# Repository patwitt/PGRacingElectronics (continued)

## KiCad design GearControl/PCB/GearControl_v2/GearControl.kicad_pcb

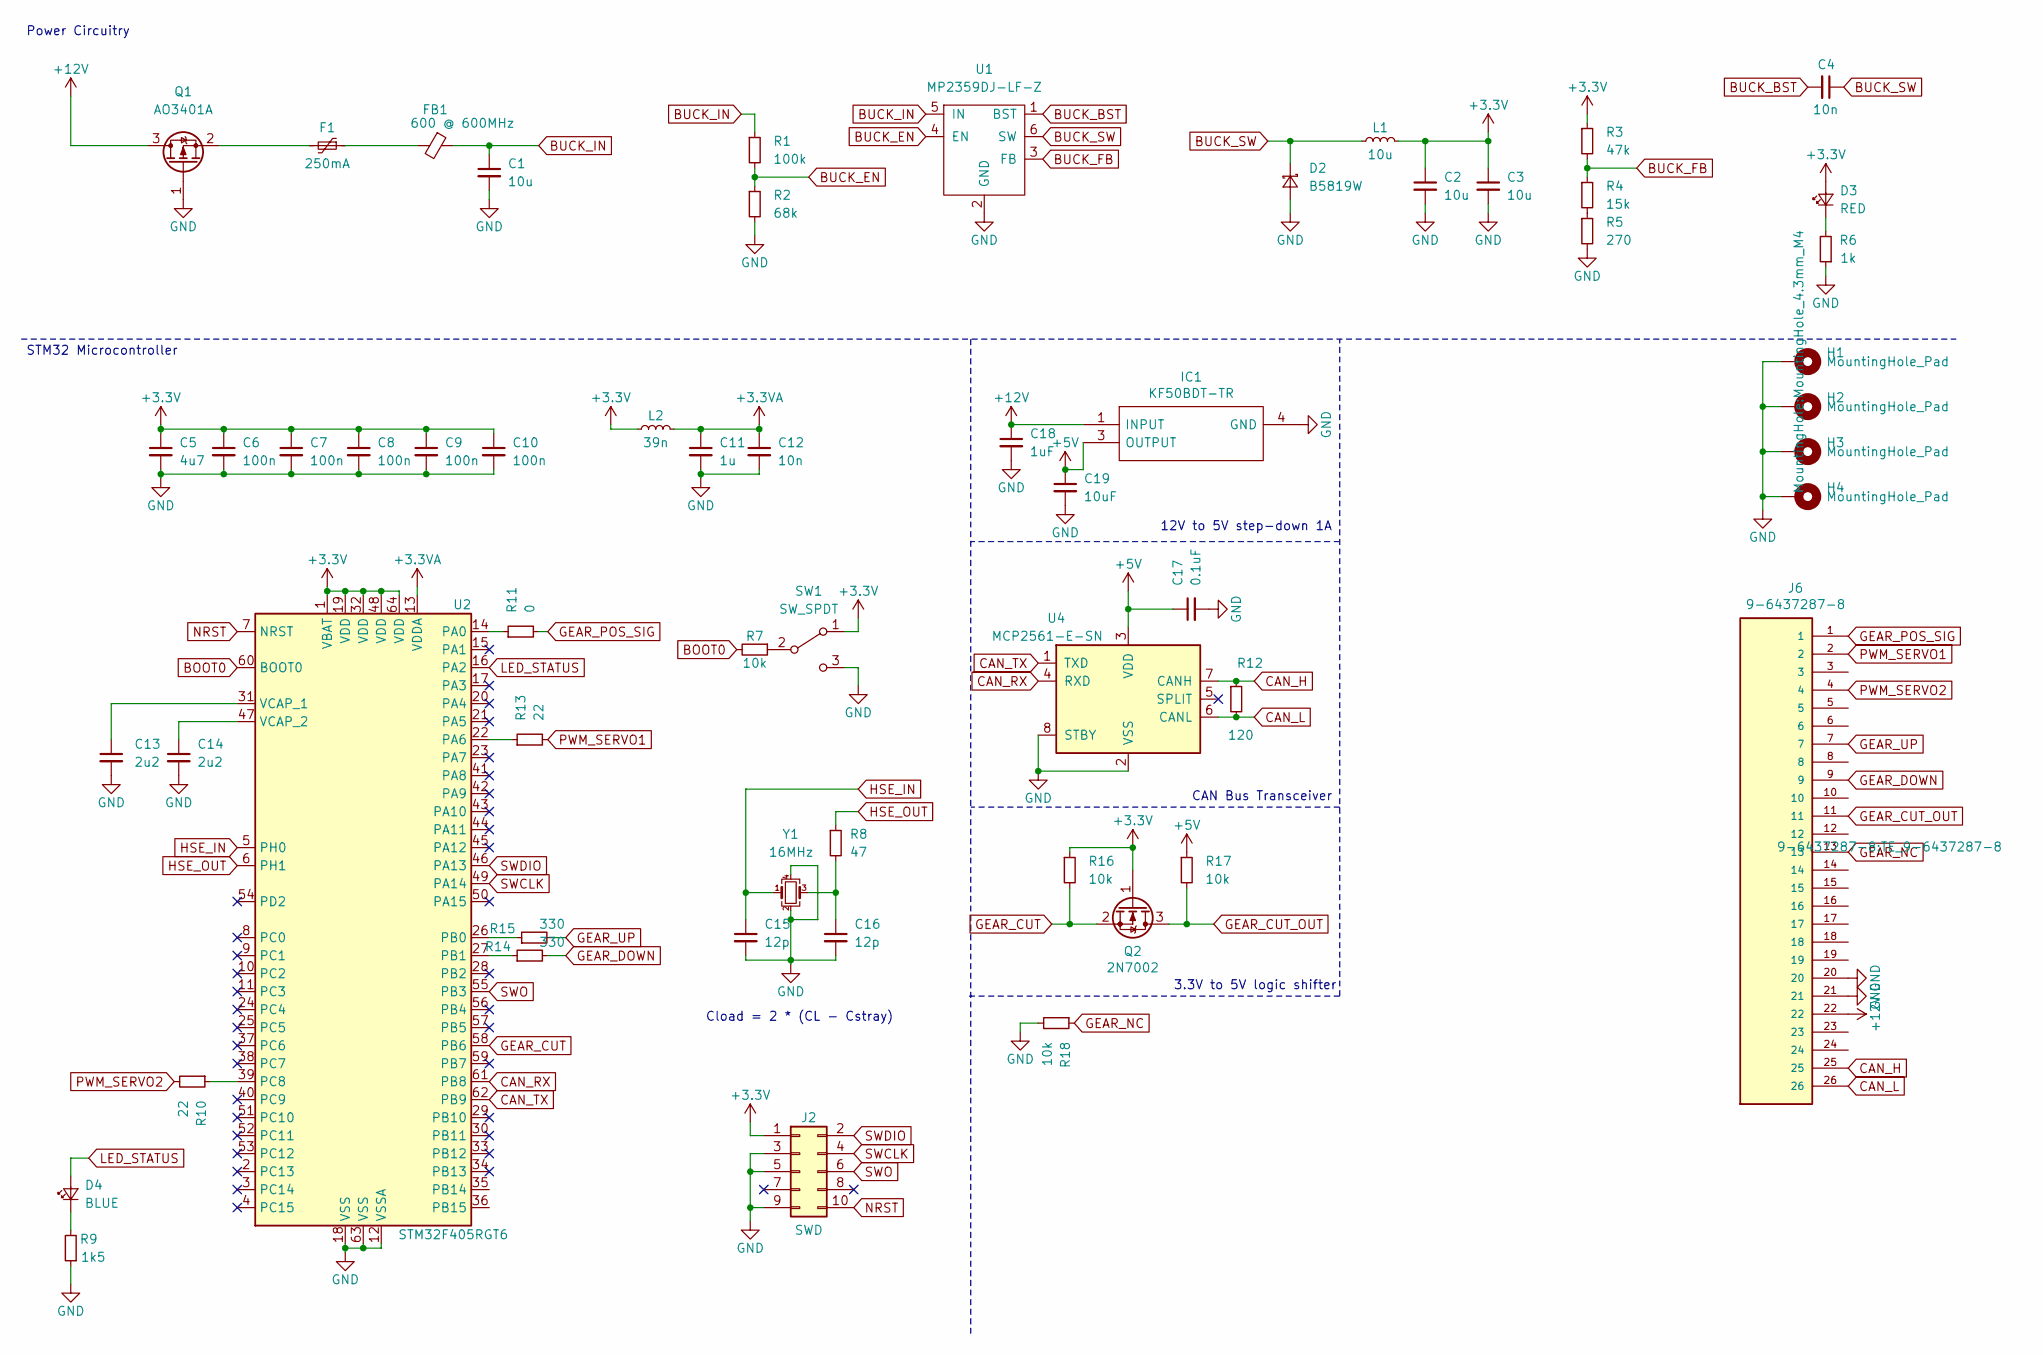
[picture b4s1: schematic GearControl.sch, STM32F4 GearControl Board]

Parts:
C1, C2, C3: 10u; C_1206_3216Metric; LCSC Part # C13585
C4: 10n; C_0603_1608Metric; LCSC Part # C57112
C5: 4u7; C_0603_1608Metric; LCSC Part # C19666
C6, C7, C8, C9, C10: 100n; C_0402_1005Metric; LCSC Part # C1525
C11: 1u; C_0402_1005Metric; LCSC Part # C52923
C12: 10n; C_0402_1005Metric; LCSC Part # C15195
C13, C14: 2u2; C_0603_1608Metric; LCSC Part # C23630
C15, C16: 12p; C_0402_1005Metric; LCSC Part # C1547
C17: 0.1uF; C_0603_1608Metric; LCSC Part # C23630
C18: 1uF; C_0805_2012Metric; LCSC Part # C1525
C19: 10uF; C_0805_2012Metric; LCSC Part # C1525
D2: B5819W; D_SOD-123; LCSC Part # C8598
D3: RED; LED_0603_1608Metric; LCSC Part # C2286
D4: BLUE; LED_0603_1608Metric; LCSC Part # C72041
F1: 250mA; Fuse_1206_3216Metric; LCSC Part # C369159
FB1: 600 @ 600MHz; L_0805_2012Metric; LCSC Part # C1017
H1, H2, H3, H4: MountingHole_Pad; MountingHole_4.3mm_M4
IC1: KF50BDT-TR; DPAK; Manufacturer_Part_Number KF50BDT-TR; Mouser Part Number 511-KF50BDT-TR
J2: SWD; PinHeader_2x05_P1.27mm_Vertical_SMD
J6: 9-6437287-8; TE_9-6437287-8; PARTREV A1
L1: 10u; L_Sunlord_MWSA0518_5.4x5.2mm; LCSC Part # C139506
L2: 39n; L_0402_1005Metric; LCSC Part # C26443
Q1: AO3401A; SOT-23; LCSC Part # C15127
Q2: 2N7002; SOT-23
R1: 100k; R_0603_1608Metric; LCSC Part # C25803
R2: 68k; R_0603_1608Metric; LCSC Part # C23231
R3: 47k; R_0603_1608Metric; LCSC Part # C25819
R4: 15k; R_0603_1608Metric; LCSC Part # C22809
R5: 270; R_0603_1608Metric; LCSC Part # C22966
R6: 1k; R_0603_1608Metric; LCSC Part # C21190
R7: 10k; R_0402_1005Metric; LCSC Part # C25744
R8: 47; R_0402_1005Metric; LCSC Part # C25118
R9: 1k5; R_0603_1608Metric; LCSC Part # C22843
R10, R13: 22; R_0603_1608Metric; LCSC Part # C25803
R11: 0; R_0603_1608Metric; LCSC Part # C25803
R12: 120; R_0603_1608Metric
R14, R15: 330; R_0603_1608Metric; LCSC Part # C25803
R16, R17, R18: 10k; R_0603_1608Metric; LCSC Part # C23231
SW1: SW_SPDT; SW_SPDT_PCM12
U1: MP2359DJ-LF-Z; SOT-23-6; LCSC Part # C14259
U2: STM32F405RGT6; LQFP-64_10x10mm_P0.5mm; LCSC Part # C15742
U4: MCP2561-E-SN; SOIC-8_3.9x4.9mm_P1.27mm
Y1: 16MHz; Crystal_SMD_3225-4Pin_3.2x2.5mm; LCSC Part # C13738

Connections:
+3.3VA: C11.1, C12.1, L2.2, U2.13 (VDDA)
+3V3: C2.1, C3.1, C5.1, C6.1, C7.1, C8.1, C9.1, C10.1, D3.2 (A), J2.1, L1.2, L2.1, Q2.1 (G), R3.1, R16.1, SW1.1 (A), U2.1 (VBAT), U2.19 (VDD), U2.32 (VDD), U2.48 (VDD), U2.64 (VDD)
+5V: C17.1, C19.1, IC1.3 (OUTPUT), R17.1, U4.3 (VDD)
+12V: C18.1, IC1.1 (INPUT), J6.22, Q1.3 (D)
BOOT0: R7.2, U2.60 (BOOT0)
BUCK_BST: C4.2, U1.1 (BST)
BUCK_EN: R1.2, R2.1, U1.4 (EN)
BUCK_FB: R3.2, R4.1, U1.3 (FB)
BUCK_IN: C1.1, FB1.1, R1.1, U1.5 (IN)
BUCK_SW: C4.1, D2.1 (K), L1.1, U1.6 (SW)
CAN_H: J6.25, R12.1, U4.7 (CANH)
CAN_L: J6.26, R12.2, U4.6 (CANL)
CAN_RX: U2.61 (PB8), U4.4 (RXD)
CAN_TX: U2.62 (PB9), U4.1 (TXD)
GEAR_CUT: Q2.2 (S), R16.2, U2.58 (PB6)
GEAR_CUT_OUT: J6.11, Q2.3 (D), R17.2
GEAR_DOWN: J6.9, R14.2
GEAR_NC: J6.13, R18.1
GEAR_POS_SIG: J6.1, R11.2
GEAR_UP: J6.7, R15.2
GND: C1.2, C2.2, C3.2, C5.2, C6.2, C7.2, C8.2, C9.2, C10.2, C11.2, C12.2, C13.2, C14.2, C15.2, C16.2, C17.2, C18.2, C19.2, D2.2 (A), H1.1, H2.1, H3.1, H4.1, IC1.4 (GND), J2.3, J2.5, J2.9, J6.20, J6.21, Q1.1 (G), R2.2, R5.2, R6.1, R9.1, R18.2, SW1.3 (C), U1.2 (GND), U2.12 (VSSA), U2.18 (VSS), U2.63 (VSS), U4.2 (VSS), U4.8 (STBY), Y1.2, Y1.4
HSE_IN: C15.1, U2.5 (PH0), Y1.1
HSE_OUT: R8.1, U2.6 (PH1)
LED_STATUS: D4.2 (A), U2.16 (PA2)
NRST: J2.10, U2.7 (NRST)
unnamed: C13.1, U2.31 (VCAP_1)
unnamed: C14.1, U2.47 (VCAP_2)
unnamed: C16.1, R8.2, Y1.3
unnamed: D3.1 (K), R6.2
unnamed: D4.1 (K), R9.2
unnamed: F1.1, FB1.2
unnamed: F1.2, Q1.2 (S)
unnamed: R4.2, R5.1
unnamed: R7.1, SW1.2 (B)
unnamed: R10.1, U2.39 (PC8)
unnamed: R11.1, U2.14 (PA0)
unnamed: R13.1, U2.22 (PA6)
unnamed: R14.1, U2.27 (PB1)
unnamed: R15.1, U2.26 (PB0)
PWM_SERVO1: J6.2, R13.2
PWM_SERVO2: J6.4, R10.2
SWCLK: J2.4, U2.49 (PA14)
SWDIO: J2.2, U2.46 (PA13)
SWO: J2.6, U2.55 (PB3)

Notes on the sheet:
Cload = 2 * (CL - Cstray)
STM32 Microcontroller
Power Circuitry
CAN Bus Transceiver
12V to 5V step-down 1A
3.3V to 5V logic shifter

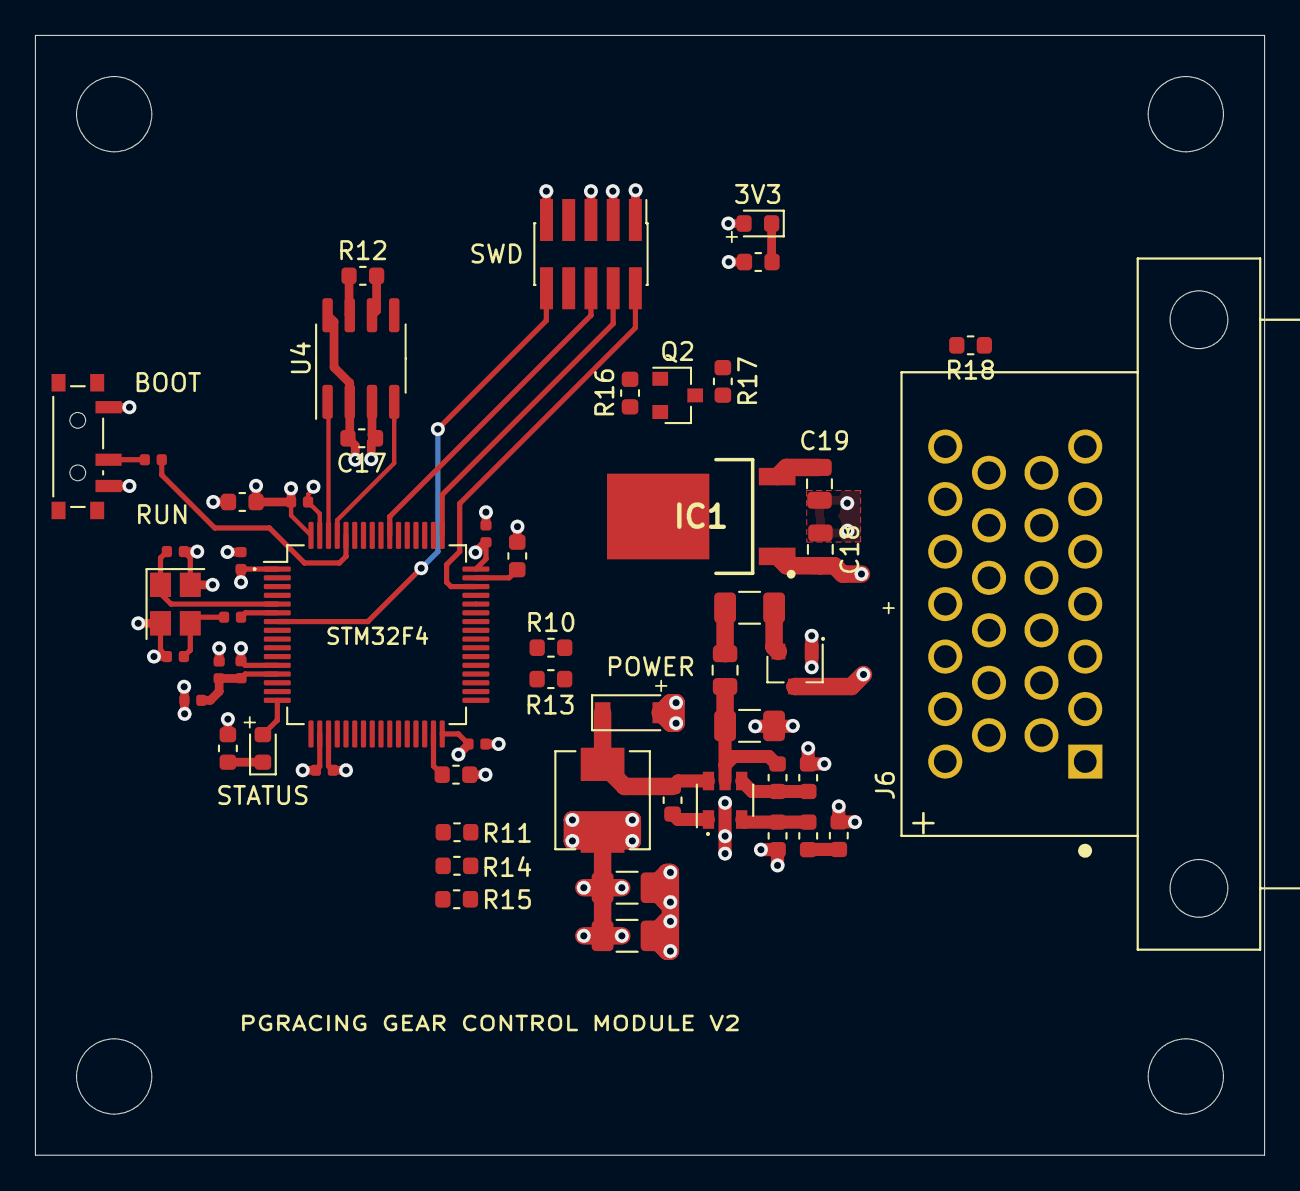
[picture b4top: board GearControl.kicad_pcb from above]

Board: 4 copper layers, 70.2 x 64.0 mm, 58 parts (0 on the bottom side), 44 nets.

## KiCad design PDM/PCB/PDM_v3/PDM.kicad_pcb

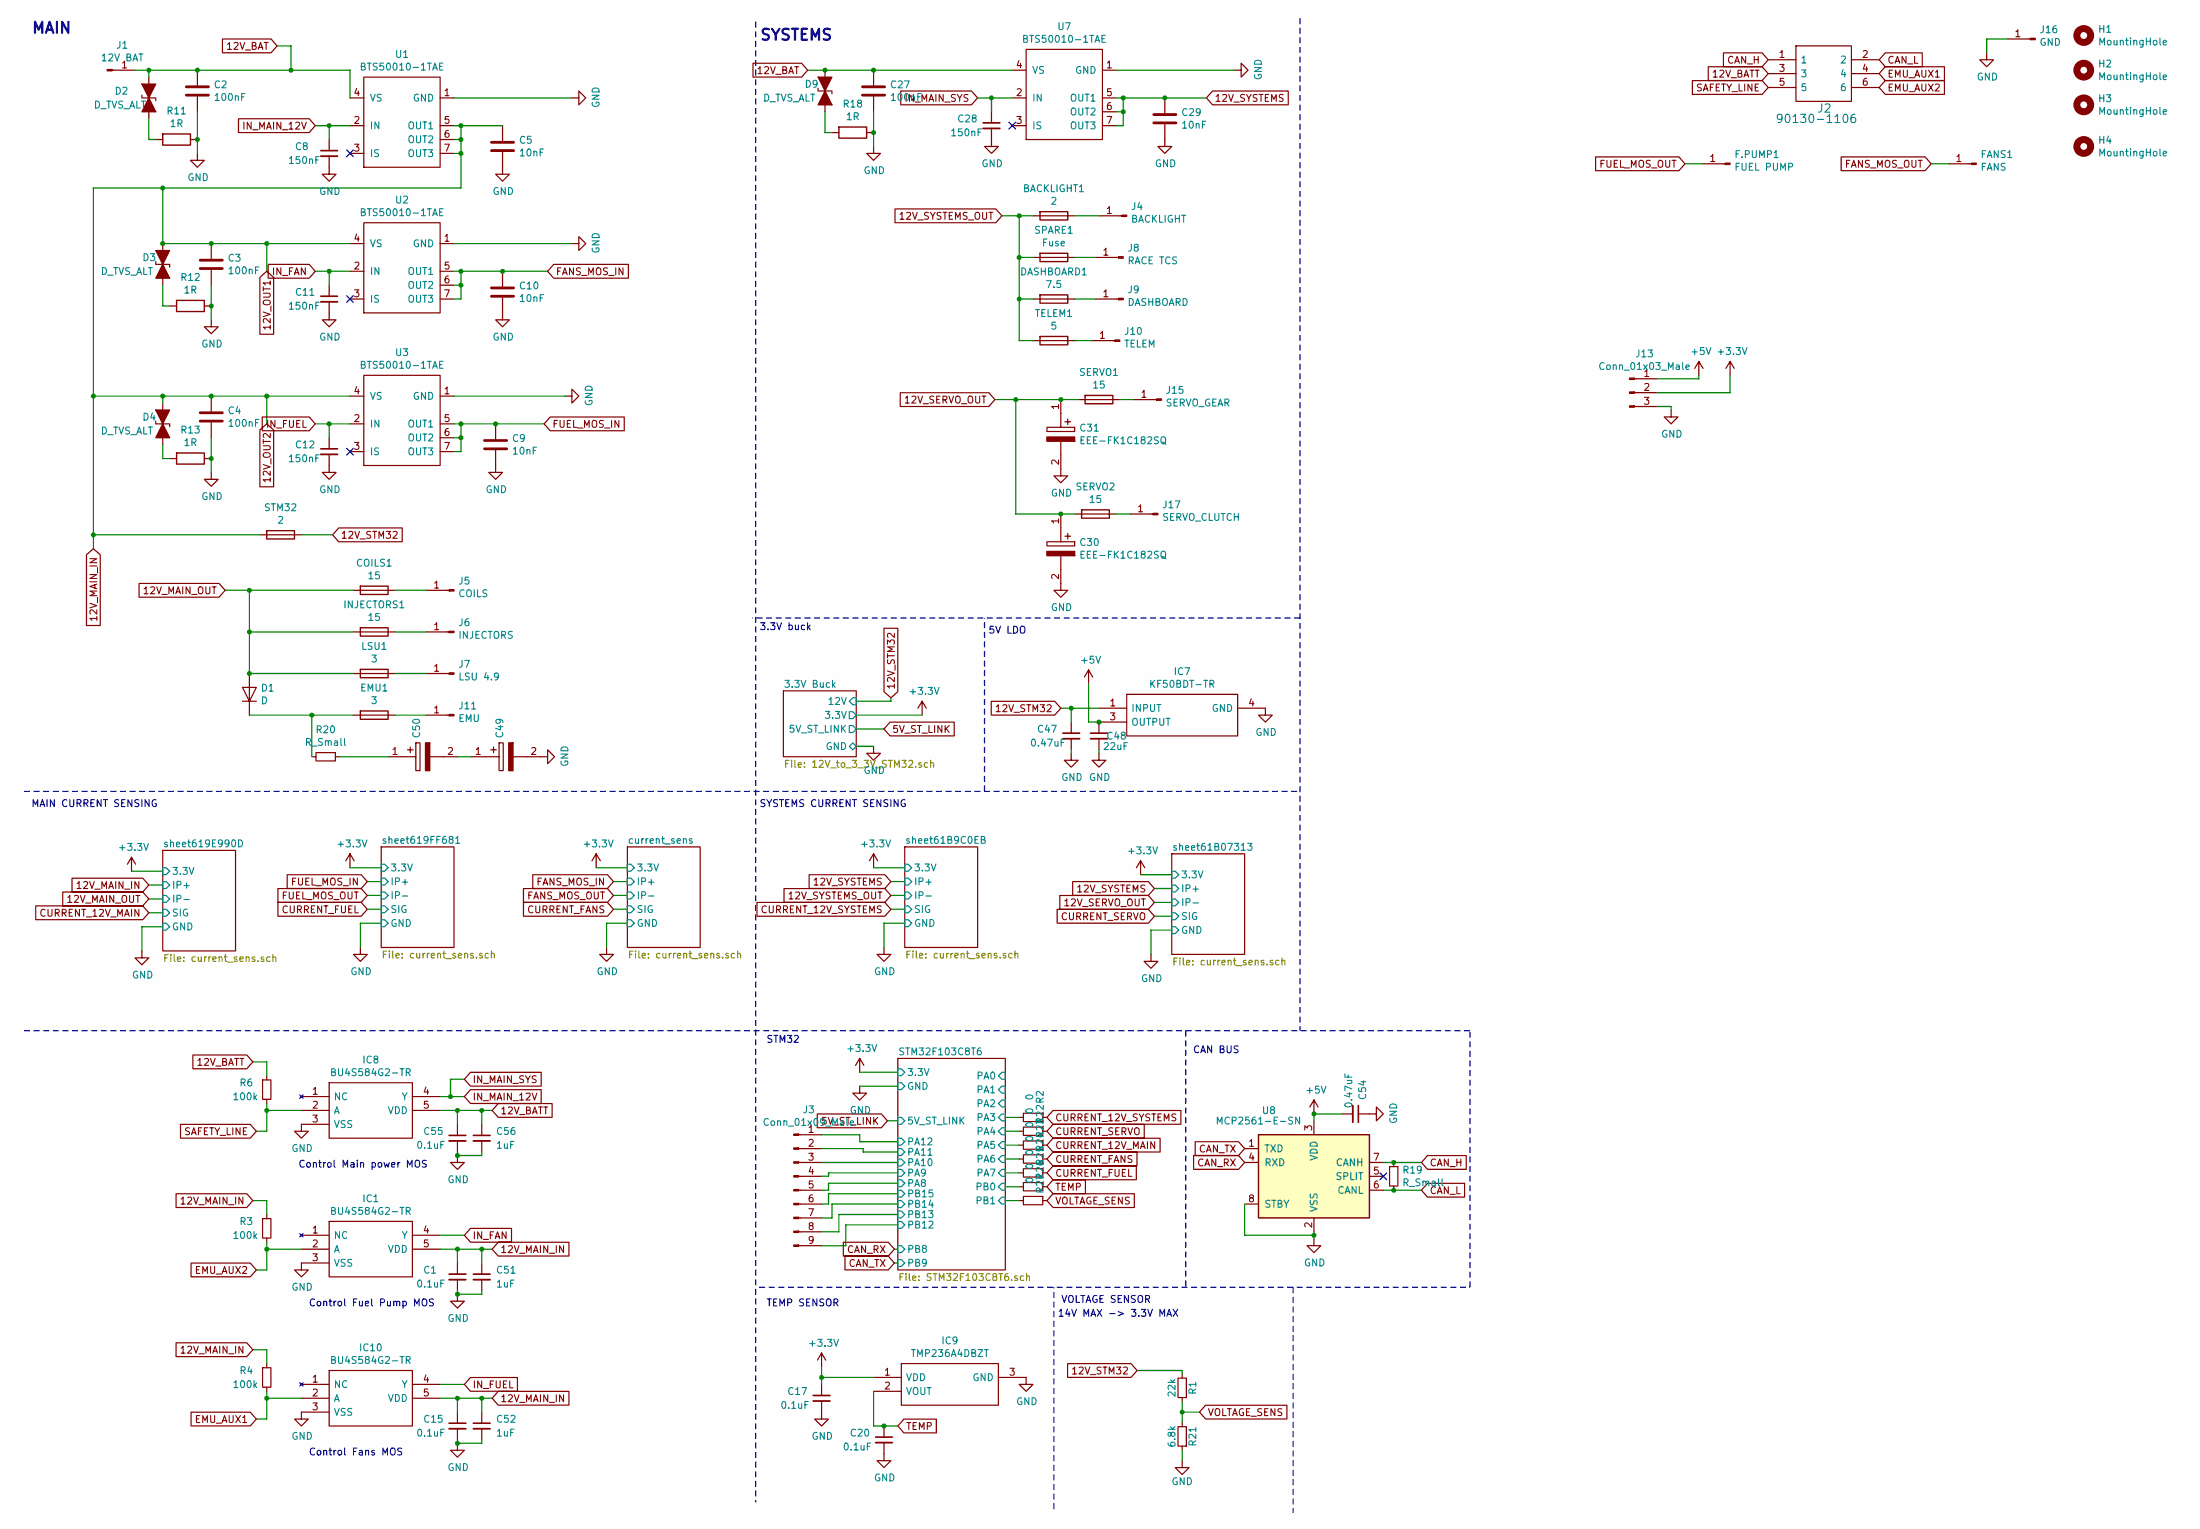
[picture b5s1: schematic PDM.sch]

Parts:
BACKLIGHT1: 2; Fuse_1206_3216Metric
C1, C15, C17, C20, C55: 0.1uF; C_0603_1608Metric
C2, C3, C4, C27: 100nF; C_0805_2012Metric_Pad1.15x1.40mm_HandSolder
C5, C9, C10, C29: 10nF; C_0805_2012Metric_Pad1.15x1.40mm_HandSolder
C8, C11, C12, C28: 150nF; C_0603_1608Metric
C30, C31: EEE-FK1C182SQ; EEEFK0J332AQ; Manufacturer_Part_Number EEE-FK1C182SQ; Mouser Part Number 667-EEE-FK1C182SQ
C47, C54: 0.47uF; C_0603_1608Metric
C48: 22uF; C_0603_1608Metric
C49, C50: SCMR18H105PRBB0; Manufacturer_Part_Number SCMR18H105PRBB0; Mouser Part Number 581-SCMR18H105PRBB0
C51, C52, C56: 1uF; C_0603_1608Metric
COILS1: 15; Fuse_1206_3216Metric
D1: D; D_SMC_Handsoldering
D2, D3, D4, D9: D_TVS_ALT; D_SMA_Handsoldering
DASHBOARD1: 7.5; Fuse_1206_3216Metric
EMU1: 3; Fuse_1206_3216Metric
F.PUMP1: FUEL PUMP; MountingHole_2.5mm_Pad_Via
FANS1: FANS; MountingHole_2.5mm_Pad_Via
H1, H2, H3, H4: MountingHole; MountingHole_3mm
IC1, IC8, IC10: BU4S584G2-TR; SOT95P280X125-5N; Manufacturer_Part_Number BU4S584G2-TR; Mouser Part Number 755-BU4S584G2-TR
IC7: KF50BDT-TR; TO228P972X240-3N; Manufacturer_Part_Number KF50BDT-TR; Mouser Part Number 511-KF50BDT-TR
IC9: TMP236A4DBZT; SOT95P237X112-3N; Manufacturer_Part_Number TMP236A4DBZT; Mouser Part Number 595-TMP236A4DBZT
INJECTORS1: 15; Fuse_1206_3216Metric
J1: 12V BAT; MountingHole_4mm_Pad_Via
J2: 90130-1106; SHDR6W65P254_2X3_996X975X1110P
J3: Conn_01x09_Male; PinHeader_1x09_P1.27mm_Vertical
J4: BACKLIGHT; MountingHole_2.2mm_M2_DIN965_Pad
J5: COILS; MountingHole_2.2mm_M2_DIN965_Pad
J6: INJECTORS; MountingHole_2.2mm_M2_DIN965_Pad
J7: LSU 4.9; MountingHole_2.2mm_M2_DIN965_Pad
J8: RACE TCS; MountingHole_2.2mm_M2_DIN965_Pad
J9: DASHBOARD; MountingHole_2.2mm_M2_DIN965_Pad
J10: TELEM; MountingHole_2.2mm_M2_DIN965_Pad
J11: EMU; MountingHole_2.2mm_M2_DIN965_Pad
J13: Conn_01x03_Male; PinHeader_1x03_P2.54mm_Vertical
J15: SERVO_GEAR; MountingHole_2.2mm_M2_DIN965_Pad
J16: GND; MountingHole_4mm_Pad_Via
J17: SERVO_CLUTCH; MountingHole_2.2mm_M2_DIN965_Pad
LSU1: 3; Fuse_1206_3216Metric
R1: 22k; R_0603_1608Metric; LCSC Part # C25744
R2, R22, R23, R24, R25, R26, R27: 0; R_0603_1608Metric
R3, R4, R6: 100k; R_0805_2012Metric
R11, R12, R13, R18: 1R; R_0603_1608Metric_Pad1.05x0.95mm_HandSolder
R19: R_Small; R_0603_1608Metric
R20: R_Small; R_1210_3225Metric
R21: 6.8k; R_0603_1608Metric; LCSC Part # C25744
SERVO1, SERVO2: 15; Fuse_1206_3216Metric
SPARE1: Fuse; Fuse_1206_3216Metric
STM32: 2; Fuse_0805_2012Metric
TELEM1: 5; Fuse_1206_3216Metric
U1, U2, U3, U7: BTS50010-1TAE; TO-263-7_TabPin4
U8: MCP2561-E-SN; SOIC-8_3.9x4.9mm_P1.27mm

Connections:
12V_BAT: C2.1, C27.1, D2.1 (A1), D9.1 (A1), J1.1, U1.4 (VS), U7.4 (VS)
12V_BATT: C55.1, C56.1, IC8.5 (VDD), J2.3, R6.1
12V_MAIN_IN: C1.1, C3.1, C4.1, C5.1, C15.1, C51.1, C52.1, D3.1 (A1), D4.1 (A1), IC1.5 (VDD), IC10.5 (VDD), R3.1, R4.1, STM32.2, U1.5 (OUT1), U1.6 (OUT2), U1.7 (OUT3), U2.4 (VS), U3.4 (VS); also elsewhere on the board
12V_MAIN_OUT: COILS1.2, D1.2 (A), INJECTORS1.2, LSU1.2; also elsewhere on the board
12V_SERVO_OUT: C30.1, C31.1, SERVO1.2, SERVO2.2; also elsewhere on the board
12V_STM32: C47.1, IC7.1 (INPUT), R1.2, STM32.1; also elsewhere on the board
12V_SYSTEMS: C29.1, U7.5 (OUT1), U7.6 (OUT2), U7.7 (OUT3); also elsewhere on the board
12V_SYSTEMS_OUT: BACKLIGHT1.2, DASHBOARD1.2, SPARE1.2, TELEM1.2; also elsewhere on the board
+3V3: C17.1, IC9.1 (VDD), J13.2; also elsewhere on the board
+5V: C48.1, C54.2, IC7.3 (OUTPUT), J13.1, U8.3 (VDD)
/STM32F103C8T6/PA3: R2.2; also elsewhere on the board
/STM32F103C8T6/PA4: R22.2; also elsewhere on the board
/STM32F103C8T6/PA5: R23.2; also elsewhere on the board
/STM32F103C8T6/PA6: R24.2; also elsewhere on the board
/STM32F103C8T6/PA7: R25.2; also elsewhere on the board
/STM32F103C8T6/PA8: J3.5; also elsewhere on the board
/STM32F103C8T6/PA9: J3.4; also elsewhere on the board
/STM32F103C8T6/PA10: J3.3; also elsewhere on the board
/STM32F103C8T6/PA11: J3.2; also elsewhere on the board
/STM32F103C8T6/PA12: J3.1; also elsewhere on the board
/STM32F103C8T6/PB0: R26.2; also elsewhere on the board
/STM32F103C8T6/PB1: R27.2; also elsewhere on the board
/STM32F103C8T6/PB12: J3.9; also elsewhere on the board
/STM32F103C8T6/PB13: J3.8; also elsewhere on the board
/STM32F103C8T6/PB14: J3.7; also elsewhere on the board
/STM32F103C8T6/PB15: J3.6; also elsewhere on the board
CAN_H: J2.1, R19.1, U8.7 (CANH)
CAN_L: J2.2, R19.2, U8.6 (CANL)
CAN_RX: U8.4 (RXD); also elsewhere on the board
CAN_TX: U8.1 (TXD); also elsewhere on the board
CURRENT_12V_MAIN: R23.1; also elsewhere on the board
CURRENT_12V_SYSTEMS: R2.1; also elsewhere on the board
CURRENT_FANS: R24.1; also elsewhere on the board
CURRENT_FUEL: R25.1; also elsewhere on the board
CURRENT_SERVO: R22.1; also elsewhere on the board
EMU_AUX1: IC10.2 (A), J2.4, R4.2
EMU_AUX2: IC1.2 (A), J2.6, R3.2
FANS_MOS_IN: C10.1, U2.5 (OUT1), U2.6 (OUT2), U2.7 (OUT3); also elsewhere on the board
FANS_MOS_OUT: FANS1.1; also elsewhere on the board
FUEL_MOS_IN: C9.1, U3.5 (OUT1), U3.6 (OUT2), U3.7 (OUT3); also elsewhere on the board
FUEL_MOS_OUT: F.PUMP1.1; also elsewhere on the board
GND: C1.2, C2.2, C3.2, C4.2, C5.2, C8.2, C9.2, C10.2, C11.2, C12.2, C15.2, C17.2, C20.2, C27.2, C28.2, C29.2, C30.2, C31.2, C47.2, C48.2, C49.2, C51.2, C52.2, C54.1, C55.2, C56.2, IC1.3 (VSS), IC7.4 (GND), IC8.3 (VSS), IC9.3 (GND), IC10.3 (VSS), J13.3, J16.1, R11.1, R12.1, R13.1, R18.1, R21.1, U1.1 (GND), U2.1 (GND), U3.1 (GND), U7.1 (GND), U8.2 (VSS), U8.8 (STBY); also elsewhere on the board
IN_FAN: C11.1, IC1.4 (Y), U2.2 (IN)
IN_FUEL: C12.1, IC10.4 (Y), U3.2 (IN)
IN_MAIN_12V: C8.1, C28.1, IC8.4 (Y), U1.2 (IN), U7.2 (IN)
unnamed: BACKLIGHT1.1, J4.1
unnamed: C49.1, C50.2
unnamed: C50.1, R20.1
unnamed: COILS1.1, J5.1
unnamed: D1.1 (K), EMU1.2, R20.2
unnamed: D2.2 (A2), R11.2
unnamed: D3.2 (A2), R12.2
unnamed: D4.2 (A2), R13.2
unnamed: D9.2 (A2), R18.2
unnamed: DASHBOARD1.1, J9.1
unnamed: EMU1.1, J11.1
unnamed: INJECTORS1.1, J6.1
unnamed: J7.1, LSU1.1
unnamed: J8.1, SPARE1.1
unnamed: J10.1, TELEM1.1
unnamed: J15.1, SERVO1.1
unnamed: J17.1, SERVO2.1
SAFETY_LINE: IC8.2 (A), J2.5, R6.2
TEMP: C20.1, IC9.2 (VOUT), R26.1
VOLTAGE_SENS: R1.1, R21.2, R27.1

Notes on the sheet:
Control Main power MOS
TEMP SENSOR
VOLTAGE SENSOR
MAIN
SYSTEMS
MAIN CURRENT SENSING
5V LDO
3.3V buck
SYSTEMS CURRENT SENSING
CAN BUS
STM32
14V MAX -> 3.3V MAX
Control Fuel Pump MOS
Control Fans MOS

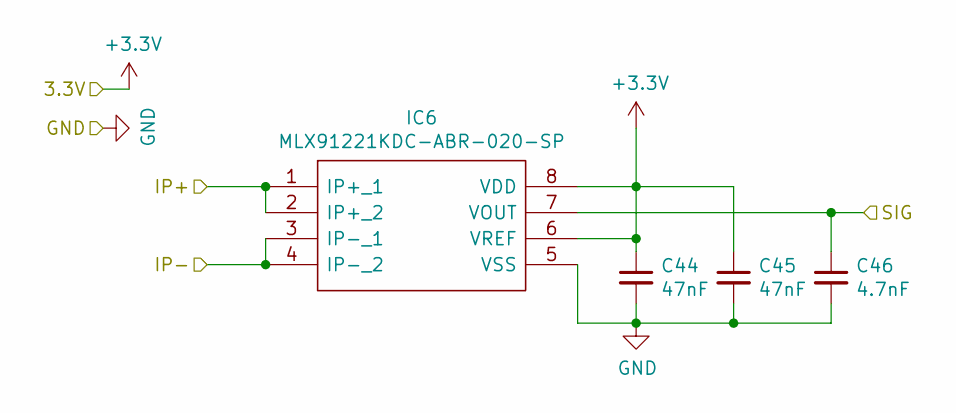
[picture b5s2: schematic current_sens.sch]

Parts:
C32, C33: 47nF; C_0603_1608Metric
C34: 4.7nF; C_0603_1608Metric
IC2: MLX91221KDC-ABR-020-SP; SOIC127P600X173-8N; Manufacturer_Part_Number MLX91221KDC-ABR-020-SP; Mouser Part Number 482-91221KDCABR020SP

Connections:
+3V3: C32.1, C33.1, IC2.6 (VREF), IC2.8 (VDD); also elsewhere on the board
CURRENT_FANS: C34.1, IC2.7 (VOUT); also elsewhere on the board
FANS_MOS_IN: IC2.1 (IP+_1), IC2.2 (IP+_2); also elsewhere on the board
FANS_MOS_OUT: IC2.3 (IP-_1), IC2.4 (IP-_2); also elsewhere on the board
GND: C32.2, C33.2, C34.2, IC2.5 (VSS); also elsewhere on the board

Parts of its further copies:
C35, C36, C38, C39, C41, C42, C44, C45: 47nF; C_0603_1608Metric
C37, C40, C43, C46: 4.7nF; C_0603_1608Metric
IC3, IC4, IC5, IC6: MLX91221KDC-ABR-020-SP; SOIC127P600X173-8N; Manufacturer_Part_Number MLX91221KDC-ABR-020-SP; Mouser Part Number 482-91221KDCABR020SP

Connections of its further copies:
12V_MAIN_IN: IC3.1 (IP+_1), IC3.2 (IP+_2); also elsewhere on the board
12V_MAIN_OUT: IC3.3 (IP-_1), IC3.4 (IP-_2); also elsewhere on the board
12V_SERVO_OUT: IC5.3 (IP-_1), IC5.4 (IP-_2); also elsewhere on the board
12V_SYSTEMS: IC5.1 (IP+_1), IC5.2 (IP+_2), IC6.1 (IP+_1), IC6.2 (IP+_2); also elsewhere on the board
12V_SYSTEMS_OUT: IC6.3 (IP-_1), IC6.4 (IP-_2); also elsewhere on the board
+3V3: C35.1, C36.1, C38.1, C39.1, C41.1, C42.1, C44.1, C45.1, IC3.6 (VREF), IC3.8 (VDD), IC4.6 (VREF), IC4.8 (VDD), IC5.6 (VREF), IC5.8 (VDD), IC6.6 (VREF), IC6.8 (VDD); also elsewhere on the board
CURRENT_12V_MAIN: C37.1, IC3.7 (VOUT); also elsewhere on the board
CURRENT_12V_SYSTEMS: C46.1, IC6.7 (VOUT); also elsewhere on the board
CURRENT_FUEL: C40.1, IC4.7 (VOUT); also elsewhere on the board
CURRENT_SERVO: C43.1, IC5.7 (VOUT); also elsewhere on the board
FUEL_MOS_IN: IC4.1 (IP+_1), IC4.2 (IP+_2); also elsewhere on the board
FUEL_MOS_OUT: IC4.3 (IP-_1), IC4.4 (IP-_2); also elsewhere on the board
GND: C35.2, C36.2, C37.2, C38.2, C39.2, C40.2, C41.2, C42.2, C43.2, C44.2, C45.2, C46.2, IC3.5 (VSS), IC4.5 (VSS), IC5.5 (VSS), IC6.5 (VSS); also elsewhere on the board

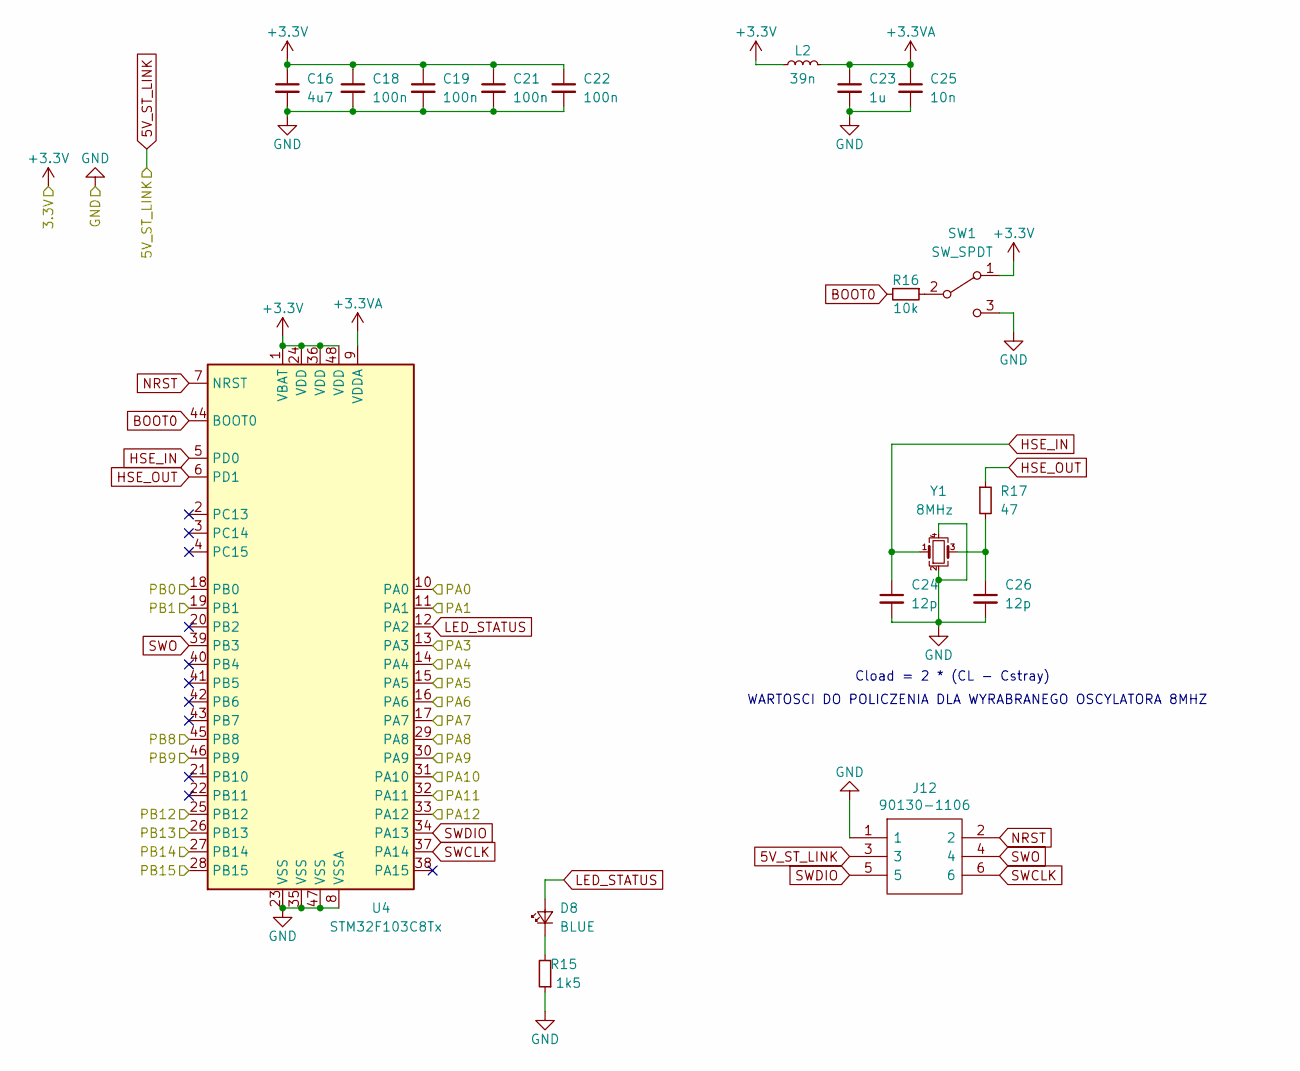
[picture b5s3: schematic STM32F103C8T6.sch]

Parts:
C16: 4u7; C_0603_1608Metric; LCSC Part # C19666
C18, C19, C21, C22: 100n; C_0402_1005Metric; LCSC Part # C1525
C23: 1u; C_0402_1005Metric; LCSC Part # C52923
C24, C26: 12p; C_0402_1005Metric; LCSC Part # C1547
C25: 10n; C_0402_1005Metric; LCSC Part # C15195
D8: BLUE; LED_0603_1608Metric; LCSC Part # C72041
J12: 90130-1106; SHDR6W65P254_2X3_996X975X1110P; Manufacturer_Part_Number 90130-1106; Mouser Part Number 538-90130-1106
L2: 39n; L_0402_1005Metric; LCSC Part # C26443
R15: 1k5; R_0603_1608Metric; LCSC Part # C22843
R16: 10k; R_0402_1005Metric; LCSC Part # C25744
R17: 47; R_0402_1005Metric; LCSC Part # C25118
SW1: SW_SPDT; SW_SPDT_PCM12
U4: STM32F103C8Tx; LQFP-48_7x7mm_P0.5mm
Y1: 8MHz; Crystal_SMD_3225-4Pin_3.2x2.5mm; LCSC Part # C13738

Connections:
5V_ST_LINK: J12.3; also elsewhere on the board
+3.3VA: C23.1, C25.1, L2.2, U4.9 (VDDA)
+3V3: C16.1, C18.1, C19.1, C21.1, C22.1, L2.1, SW1.1 (A), U4.1 (VBAT), U4.24 (VDD), U4.36 (VDD), U4.48 (VDD); also elsewhere on the board
/STM32F103C8T6/PA3: U4.13 (PA3); also elsewhere on the board
/STM32F103C8T6/PA4: U4.14 (PA4); also elsewhere on the board
/STM32F103C8T6/PA5: U4.15 (PA5); also elsewhere on the board
/STM32F103C8T6/PA6: U4.16 (PA6); also elsewhere on the board
/STM32F103C8T6/PA7: U4.17 (PA7); also elsewhere on the board
/STM32F103C8T6/PA8: U4.29 (PA8); also elsewhere on the board
/STM32F103C8T6/PA9: U4.30 (PA9); also elsewhere on the board
/STM32F103C8T6/PA10: U4.31 (PA10); also elsewhere on the board
/STM32F103C8T6/PA11: U4.32 (PA11); also elsewhere on the board
/STM32F103C8T6/PA12: U4.33 (PA12); also elsewhere on the board
/STM32F103C8T6/PB0: U4.18 (PB0); also elsewhere on the board
/STM32F103C8T6/PB1: U4.19 (PB1); also elsewhere on the board
/STM32F103C8T6/PB12: U4.25 (PB12); also elsewhere on the board
/STM32F103C8T6/PB13: U4.26 (PB13); also elsewhere on the board
/STM32F103C8T6/PB14: U4.27 (PB14); also elsewhere on the board
/STM32F103C8T6/PB15: U4.28 (PB15); also elsewhere on the board
BOOT0: R16.2, U4.44 (BOOT0)
CAN_RX: U4.45 (PB8); also elsewhere on the board
CAN_TX: U4.46 (PB9); also elsewhere on the board
GND: C16.2, C18.2, C19.2, C21.2, C22.2, C23.2, C24.2, C25.2, C26.2, J12.1, R15.1, SW1.3 (C), U4.8 (VSSA), U4.23 (VSS), U4.35 (VSS), U4.47 (VSS), Y1.2, Y1.4; also elsewhere on the board
HSE_IN: C24.1, U4.5 (PD0), Y1.1
HSE_OUT: R17.1, U4.6 (PD1)
LED_STATUS: D8.2 (A), U4.12 (PA2)
NRST: J12.2, U4.7 (NRST)
unnamed: C26.1, R17.2, Y1.3
unnamed: D8.1 (K), R15.2
unnamed: R16.1, SW1.2 (B)
SWCLK: J12.6, U4.37 (PA14)
SWDIO: J12.5, U4.34 (PA13)
SWO: J12.4, U4.39 (PB3)

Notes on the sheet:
Cload = 2 * (CL - Cstray)
WARTOSCI DO POLICZENIA DLA WYRABRANEGO OSCYLATORA 8MHZ

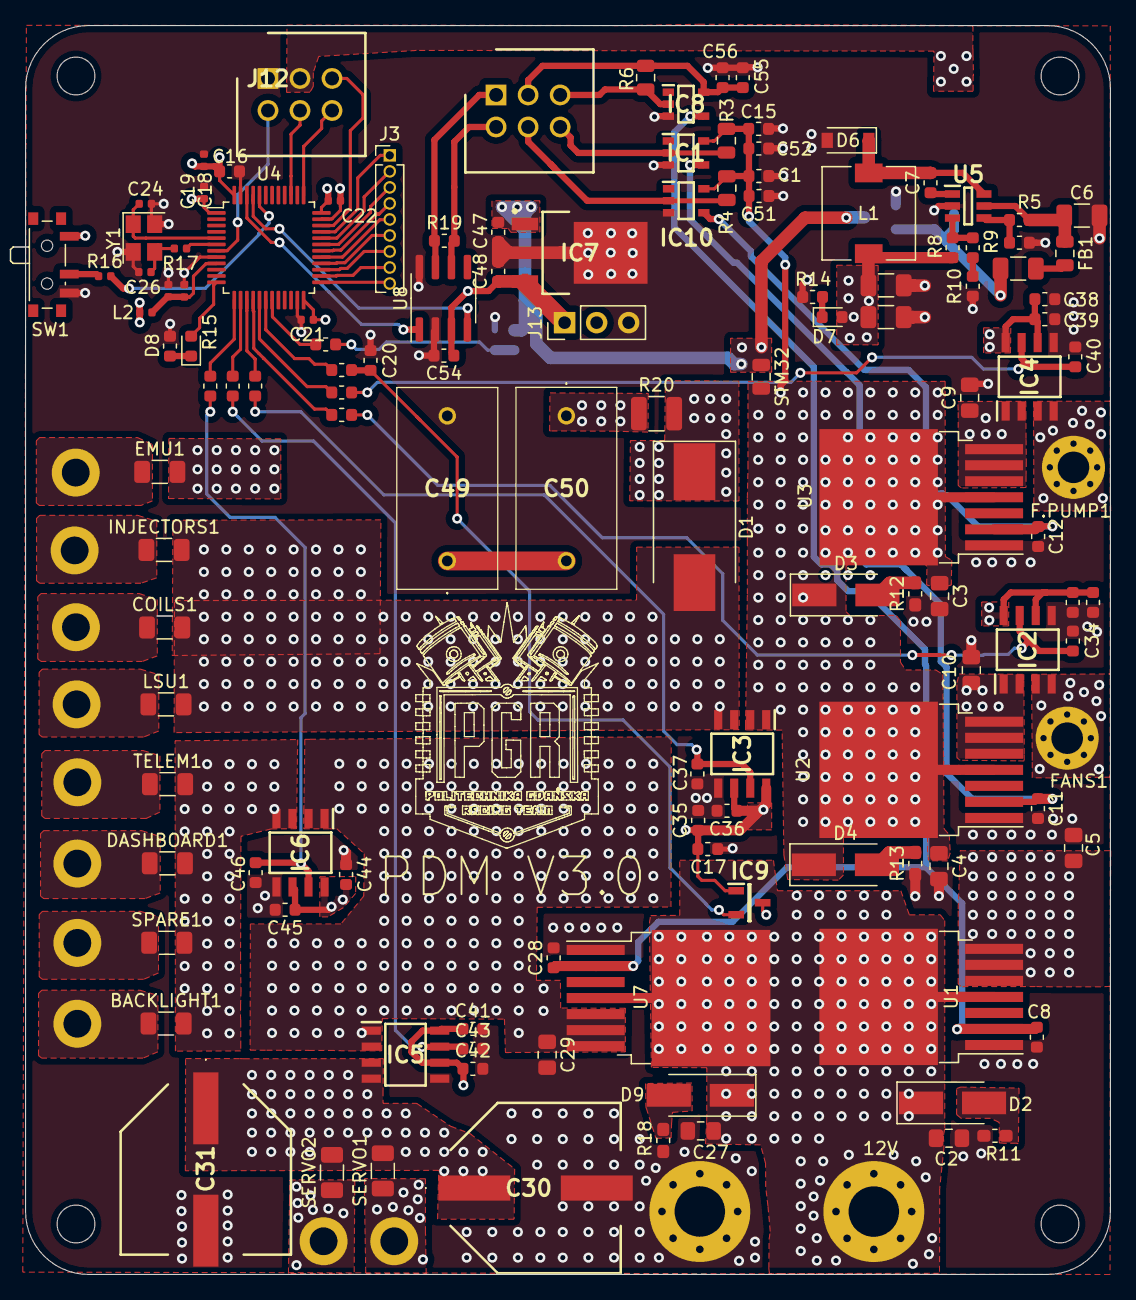
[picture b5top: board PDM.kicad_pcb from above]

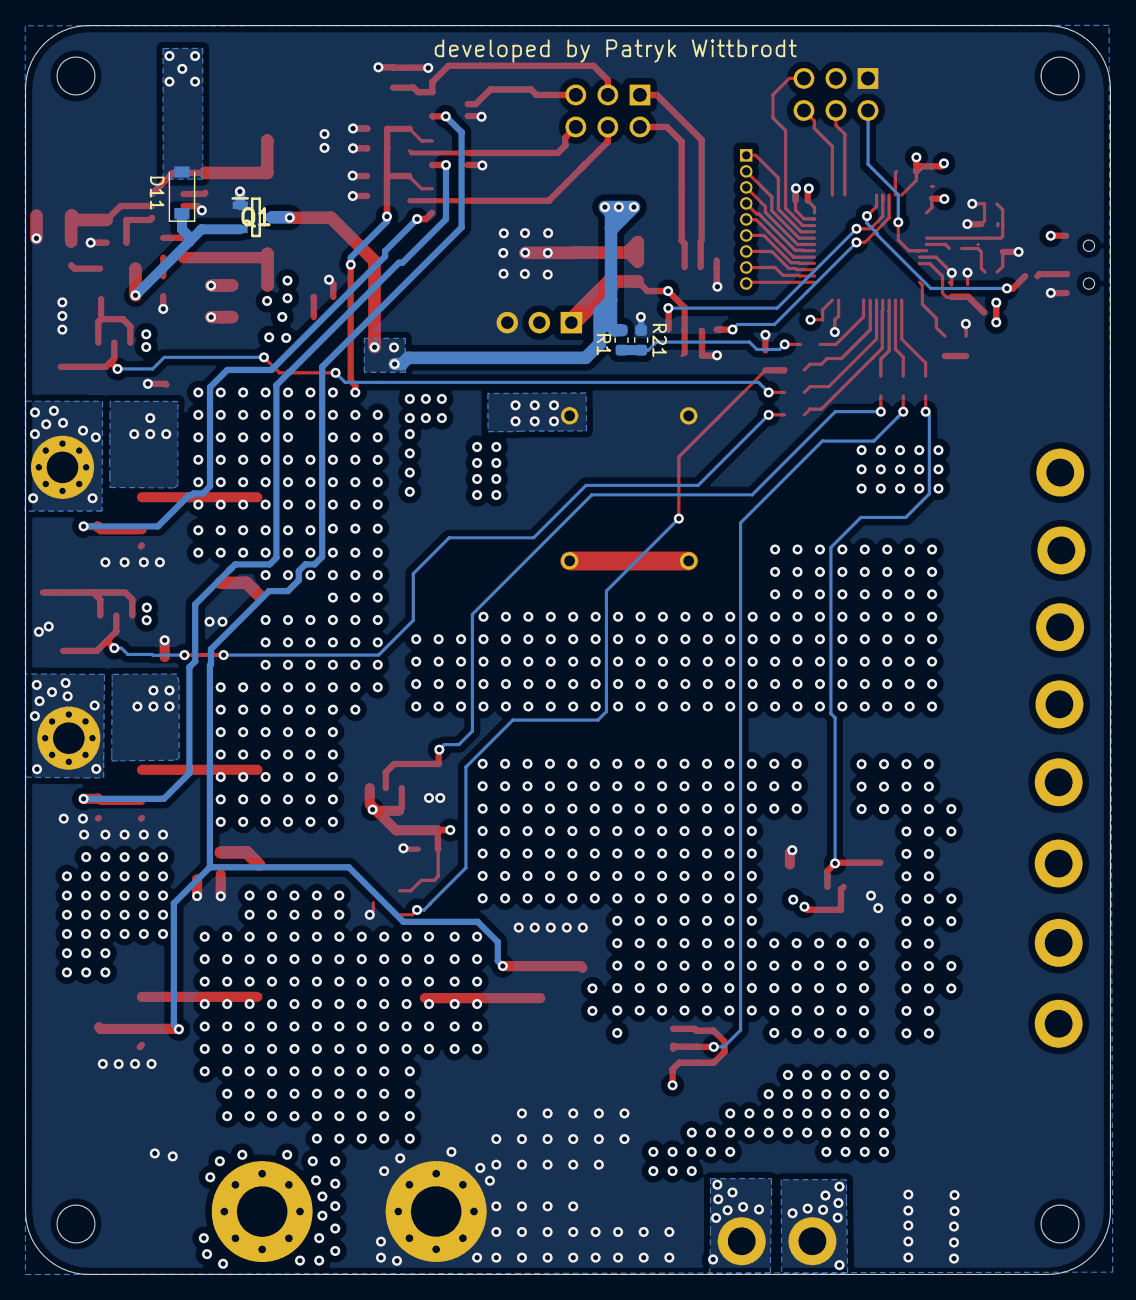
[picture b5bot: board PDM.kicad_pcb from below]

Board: 4 copper layers, 86.0 x 99.0 mm, 148 parts (4 on the bottom side), 87 nets.

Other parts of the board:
C6, C13, C14: 10uF; C_1206_3216Metric
C7: 10nF; C_0603_1608Metric
D6, D11: B5819W; D_SOD-123
D7: LED; LED_0603_1608Metric
F1: Polyfuse_Small; Fuse_1206_3216Metric
FB1: 600 @ 600Mhz; L_0805_2012Metric
L1: 10uH; L_7.3x7.3_H4.5
Q1: AO3401A; SOT95P280X125-3N
R5: 100k; R_0603_1608Metric
R7: 68k; R_0603_1608Metric
R8: 47k; R_0603_1608Metric
R9: 15k; R_0603_1608Metric
R10: 270; R_0603_1608Metric
R14: 1k; R_0603_1608Metric
U5: MP2359; SOT95P280X145-6N

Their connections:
5V_ST_LINK: D11.2; also elsewhere on the board
12V_STM32: Q1.3; also elsewhere on the board
+3V3: C13.1, C14.1, D7.2, L1.1, R8.2; also elsewhere on the board
BUCK_BST: C7.1, U5.1
BUCK_EN: R5.2, R7.1, U5.4
BUCK_FB: R8.1, R9.1, U5.3
BUCK_IN: C6.1, FB1.1, R5.1, U5.5
BUCK_SW: C7.2, D6.1, L1.2, U5.6
GND: C6.2, C13.2, C14.2, D6.2, Q1.1, R7.2, R10.2, R14.2, U5.2; also elsewhere on the board
unnamed: D7.1, R14.1
unnamed: D11.1, F1.2, Q1.2
unnamed: F1.1, FB1.2
unnamed: R9.2, R10.1
